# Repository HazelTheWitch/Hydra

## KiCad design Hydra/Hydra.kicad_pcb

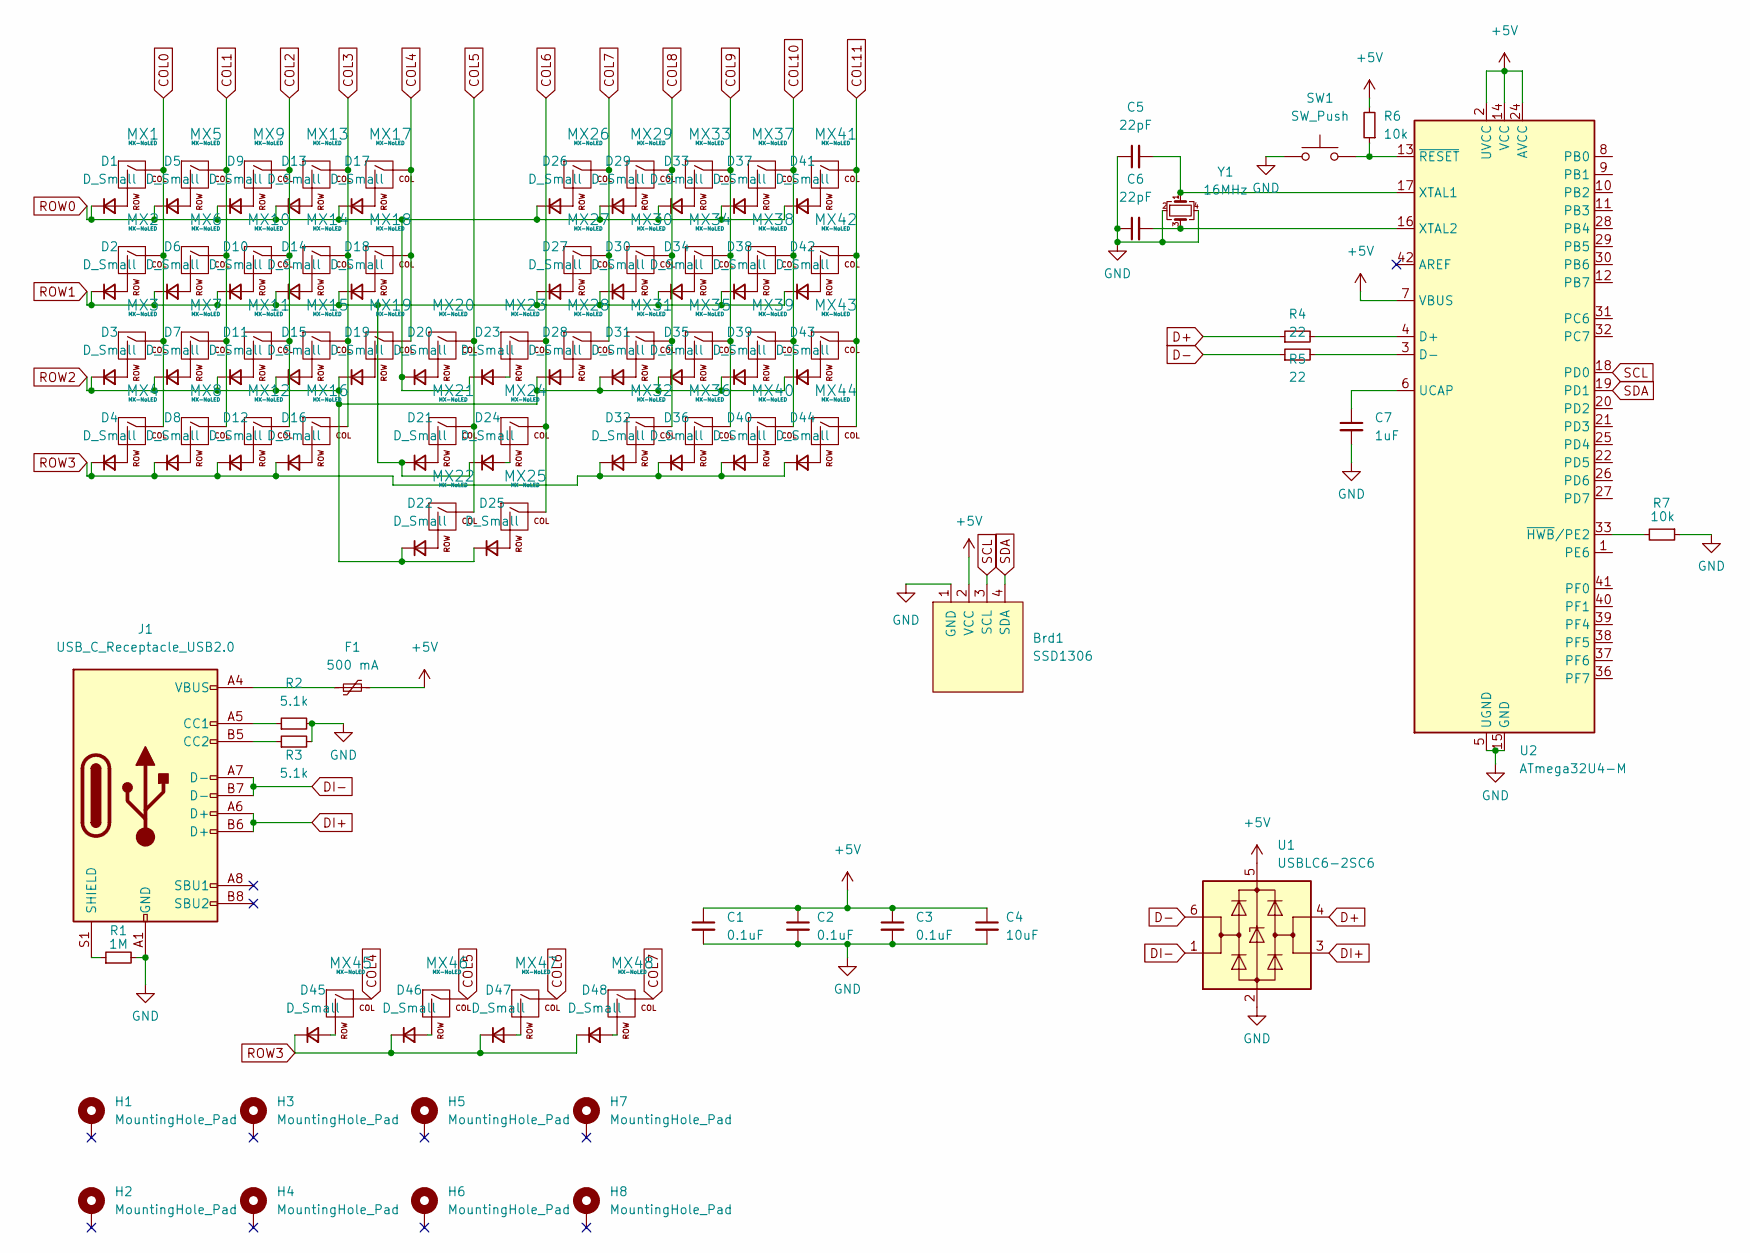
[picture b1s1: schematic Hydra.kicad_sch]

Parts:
Brd1: SSD1306; 128x64OLED
C1, C2, C3: 0.1uF; C_0805_2012Metric
C4: 10uF; C_0805_2012Metric
C5, C6: 22pF; C_0805_2012Metric
C7: 1uF; C_0805_2012Metric
D1, D2, D3, D4, D5, D6, D7, D8, D9, D10, D11, D12, D13, D14, D15, D16, D17, D18, D19, D20, D21, D22, D23, D24, D25, D26, D27, D28, D29, D30, D31, D32, D33, D34, D35, D36, D37, D38, D39, D40, D41, D42, D43, D44, D45, D46, D47, D48: D_Small; D_SOD-123
F1: 500 mA; Fuse_1206_3216Metric
H1, H2, H3, H4, H5, H6, H7, H8: MountingHole_Pad; MountingHole_2.2mm_M2_Pad
J1: USB_C_Receptacle_USB2.0; USB_C_Receptacle_GT-USB-7010
MX1, MX2, MX3, MX4, MX5, MX6, MX7, MX8, MX9, MX10, MX11, MX12, MX13, MX14, MX15, MX16, MX17, MX18, MX19, MX20, MX22, MX23, MX25, MX26, MX27, MX28, MX29, MX30, MX31, MX32, MX33, MX34, MX35, MX36, MX37, MX38, MX39, MX40, MX41, MX42, MX43, MX44, MX45, MX46, MX47, MX48: MX-NoLED; MXOnly-1U-NoLED
MX21, MX24: MX-NoLED; MXOnly-2U-NoLED
R1: 1M; R_0805_2012Metric
R2, R3: 5.1k; R_0805_2012Metric
R4, R5: 22; R_0805_2012Metric
R6, R7: 10k; R_0805_2012Metric
SW1: SW_Push; SKQG-1155865
U1: USBLC6-2SC6; SOT-23-6
U2: ATmega32U4-M; QFN-44-1EP_7x7mm_P0.5mm_EP5.2x5.2mm
Y1: 16MHz; Crystal_SMD_3225-4Pin_3.2x2.5mm

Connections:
+5V: Brd1.2 (VCC), C1.1, C2.1, C3.1, C4.1, F1.2, R6.2, U1.5 (VBUS), U2.2 (UVCC), U2.7 (VBUS), U2.14 (VCC), U2.24 (AVCC), U2.34 (VCC), U2.44 (AVCC)
COL0: MX1.1 (COL), MX2.1 (COL), MX3.1 (COL), MX4.1 (COL)
COL1: MX5.1 (COL), MX6.1 (COL), MX7.1 (COL), MX8.1 (COL)
COL2: MX9.1 (COL), MX10.1 (COL), MX11.1 (COL), MX12.1 (COL)
COL3: MX13.1 (COL), MX14.1 (COL), MX15.1 (COL), MX16.1 (COL)
COL4: MX17.1 (COL), MX18.1 (COL), MX19.1 (COL), MX45.1 (COL)
COL5: MX20.1 (COL), MX21.1 (COL), MX22.1 (COL), MX46.1 (COL)
COL6: MX23.1 (COL), MX24.1 (COL), MX25.1 (COL), MX47.1 (COL)
COL7: MX26.1 (COL), MX27.1 (COL), MX28.1 (COL), MX48.1 (COL)
COL8: MX29.1 (COL), MX30.1 (COL), MX31.1 (COL), MX32.1 (COL)
COL9: MX33.1 (COL), MX34.1 (COL), MX35.1 (COL), MX36.1 (COL)
COL10: MX37.1 (COL), MX38.1 (COL), MX39.1 (COL), MX40.1 (COL)
COL11: MX41.1 (COL), MX42.1 (COL), MX43.1 (COL), MX44.1 (COL)
D+: R5.1, U1.4 (I/O2)
D-: R4.1, U1.6 (I/O1)
DI+: J1.A6 (D+), J1.B6 (D+), U1.3 (I/O2)
DI-: J1.A7 (D-), J1.B7 (D-), U1.1 (I/O1)
GND: Brd1.1 (GND), C1.2, C2.2, C3.2, C4.2, C5.1, C6.1, C7.2, J1.A1 (GND), J1.A12 (GND), J1.B1 (GND), J1.B12 (GND), R1.2, R2.2, R3.2, R7.1, SW1.1, U1.2 (GND), U2.5 (UGND), U2.15 (GND), U2.23 (GND), U2.35 (GND), U2.43 (GND), U2.45 (GND), Y1.2, Y1.4
unnamed: C5.2, U2.17 (XTAL1), Y1.1
unnamed: C6.2, U2.16 (XTAL2), Y1.3
unnamed: C7.1, U2.6 (UCAP)
unnamed: D1.2 (A), MX1.2 (ROW)
unnamed: D2.2 (A), MX2.2 (ROW)
unnamed: D3.2 (A), MX3.2 (ROW)
unnamed: D4.2 (A), MX4.2 (ROW)
unnamed: D5.2 (A), MX5.2 (ROW)
unnamed: D6.2 (A), MX6.2 (ROW)
unnamed: D7.2 (A), MX7.2 (ROW)
unnamed: D8.2 (A), MX8.2 (ROW)
unnamed: D9.2 (A), MX9.2 (ROW)
unnamed: D10.2 (A), MX10.2 (ROW)
unnamed: D11.2 (A), MX11.2 (ROW)
unnamed: D12.2 (A), MX12.2 (ROW)
unnamed: D13.2 (A), MX13.2 (ROW)
unnamed: D14.2 (A), MX14.2 (ROW)
unnamed: D15.2 (A), MX15.2 (ROW)
unnamed: D16.2 (A), MX16.2 (ROW)
unnamed: D17.2 (A), MX17.2 (ROW)
unnamed: D18.2 (A), MX18.2 (ROW)
unnamed: D19.2 (A), MX19.2 (ROW)
unnamed: D20.2 (A), MX20.2 (ROW)
unnamed: D21.2 (A), MX21.2 (ROW)
unnamed: D22.2 (A), MX22.2 (ROW)
unnamed: D23.2 (A), MX23.2 (ROW)
unnamed: D24.2 (A), MX24.2 (ROW)
unnamed: D25.2 (A), MX25.2 (ROW)
unnamed: D26.2 (A), MX26.2 (ROW)
unnamed: D27.2 (A), MX27.2 (ROW)
unnamed: D28.2 (A), MX28.2 (ROW)
unnamed: D29.2 (A), MX29.2 (ROW)
unnamed: D30.2 (A), MX30.2 (ROW)
unnamed: D31.2 (A), MX31.2 (ROW)
unnamed: D32.2 (A), MX32.2 (ROW)
unnamed: D33.2 (A), MX33.2 (ROW)
unnamed: D34.2 (A), MX34.2 (ROW)
unnamed: D35.2 (A), MX35.2 (ROW)
unnamed: D36.2 (A), MX36.2 (ROW)
unnamed: D37.2 (A), MX37.2 (ROW)
unnamed: D38.2 (A), MX38.2 (ROW)
unnamed: D39.2 (A), MX39.2 (ROW)
unnamed: D40.2 (A), MX40.2 (ROW)
unnamed: D41.2 (A), MX41.2 (ROW)
unnamed: D42.2 (A), MX42.2 (ROW)
unnamed: D43.2 (A), MX43.2 (ROW)
unnamed: D44.2 (A), MX44.2 (ROW)
unnamed: D45.2 (A), MX45.2 (ROW)
unnamed: D46.2 (A), MX46.2 (ROW)
unnamed: D47.2 (A), MX47.2 (ROW)
unnamed: D48.2 (A), MX48.2 (ROW)
unnamed: F1.1, J1.A4 (VBUS), J1.A9 (VBUS), J1.B4 (VBUS), J1.B9 (VBUS)
unnamed: J1.A5 (CC1), R2.1
unnamed: J1.B5 (CC2), R3.1
unnamed: J1.S1 (SHIELD), R1.1
unnamed: R4.2, U2.3 (D-)
unnamed: R5.2, U2.4 (D+)
unnamed: R6.1, SW1.2, U2.13 (~RESET)
unnamed: R7.2, U2.33 (~HWB/PE2)
ROW0: D1.1 (K), D5.1 (K), D9.1 (K), D13.1 (K), D17.1 (K), D20.1 (K), D23.1 (K), D26.1 (K), D29.1 (K), D33.1 (K), D37.1 (K), D41.1 (K)
ROW1: D2.1 (K), D6.1 (K), D10.1 (K), D14.1 (K), D18.1 (K), D21.1 (K), D24.1 (K), D27.1 (K), D30.1 (K), D34.1 (K), D38.1 (K), D42.1 (K)
ROW2: D3.1 (K), D7.1 (K), D11.1 (K), D15.1 (K), D19.1 (K), D22.1 (K), D25.1 (K), D28.1 (K), D31.1 (K), D35.1 (K), D39.1 (K), D43.1 (K)
ROW3: D4.1 (K), D8.1 (K), D12.1 (K), D16.1 (K), D32.1 (K), D36.1 (K), D40.1 (K), D44.1 (K), D45.1 (K), D46.1 (K), D47.1 (K), D48.1 (K)
SCL: Brd1.3 (SCL), U2.18 (PD0)
SDA: Brd1.4 (SDA), U2.19 (PD1)

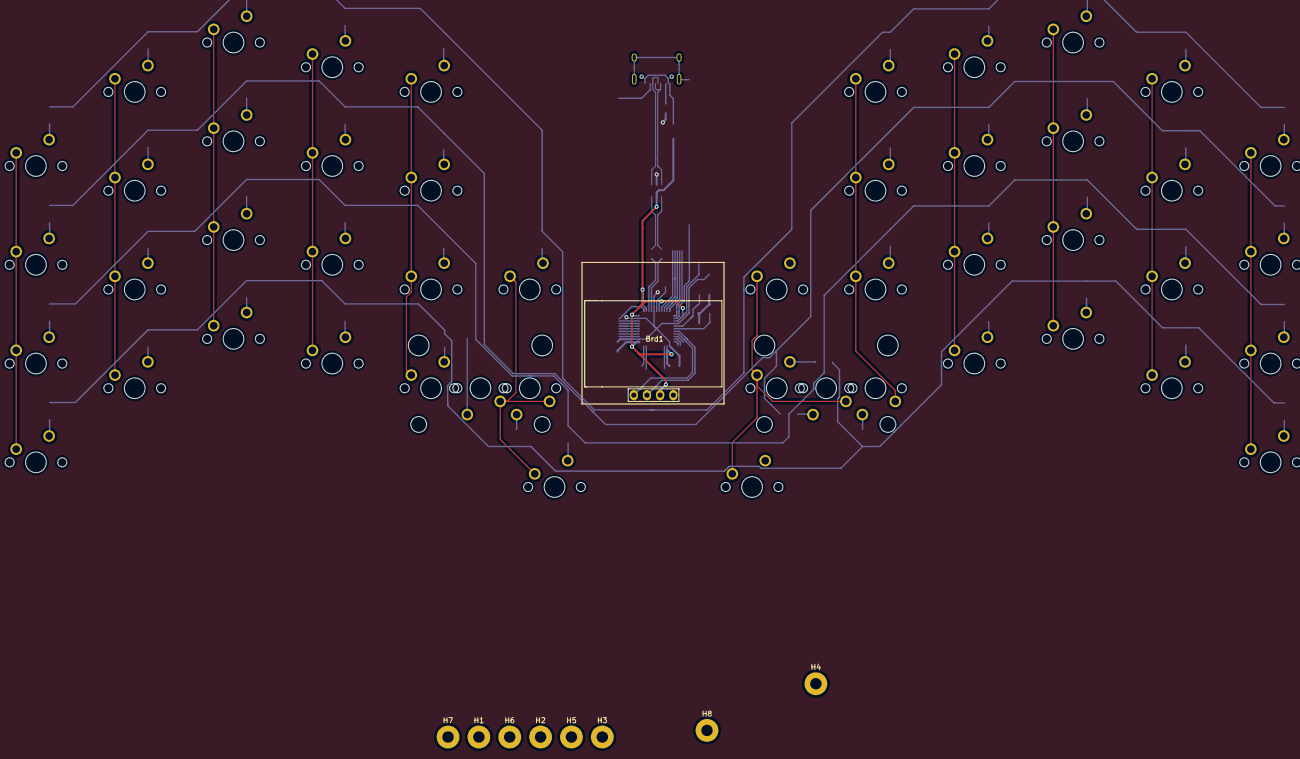
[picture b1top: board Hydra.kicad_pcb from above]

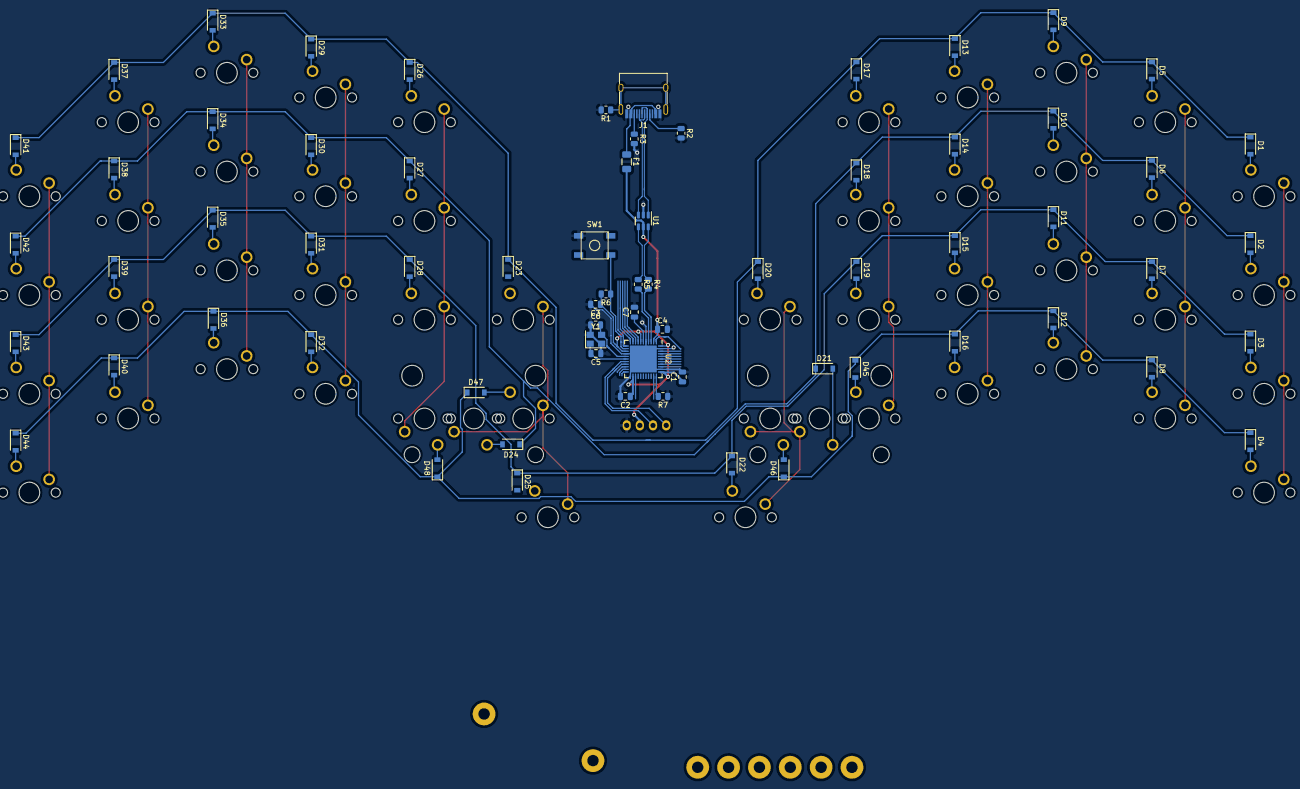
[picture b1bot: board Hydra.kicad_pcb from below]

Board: 2 copper layers, 125 parts (68 on the bottom side), 83 nets.

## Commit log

2022-05-21 Initial Files
2022-05-21 Oops lol
2022-05-21 Footprint assignment and placement of 50% switches
2022-05-21 finished layout placed diodes
2022-05-21 Fixed Schematic
2022-05-21 Cheeky matrix optimization
2022-05-21 Even more optimizations
2022-05-21 Fixed Matrix
2022-05-21 Added OLED
2022-05-21 mcu traces
2022-05-21 finished mcu routes
2022-05-21 Wired Matrix
2022-05-21 stuff
2022-05-21 Added 2 1u options for space
2022-05-21 stuff lol
2022-05-22 Centered OLED
2022-05-22 routed switch matrix and oled
